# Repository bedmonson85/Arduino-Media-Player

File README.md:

Arduino-Media-Player
====================
This is currently a place to keep up with my eagle cad files for my project:
Atmega328p /w Arduino UNO bootloader based media player design. 
It is currently unfinished -- a work in progress.  After schematic and board are finished
I'll begin work on the code.

Released under the Creative Commons Attribution Share-Alike 4.0 License.
https:/creativecommons.org/licenses/by-sa/4.0/

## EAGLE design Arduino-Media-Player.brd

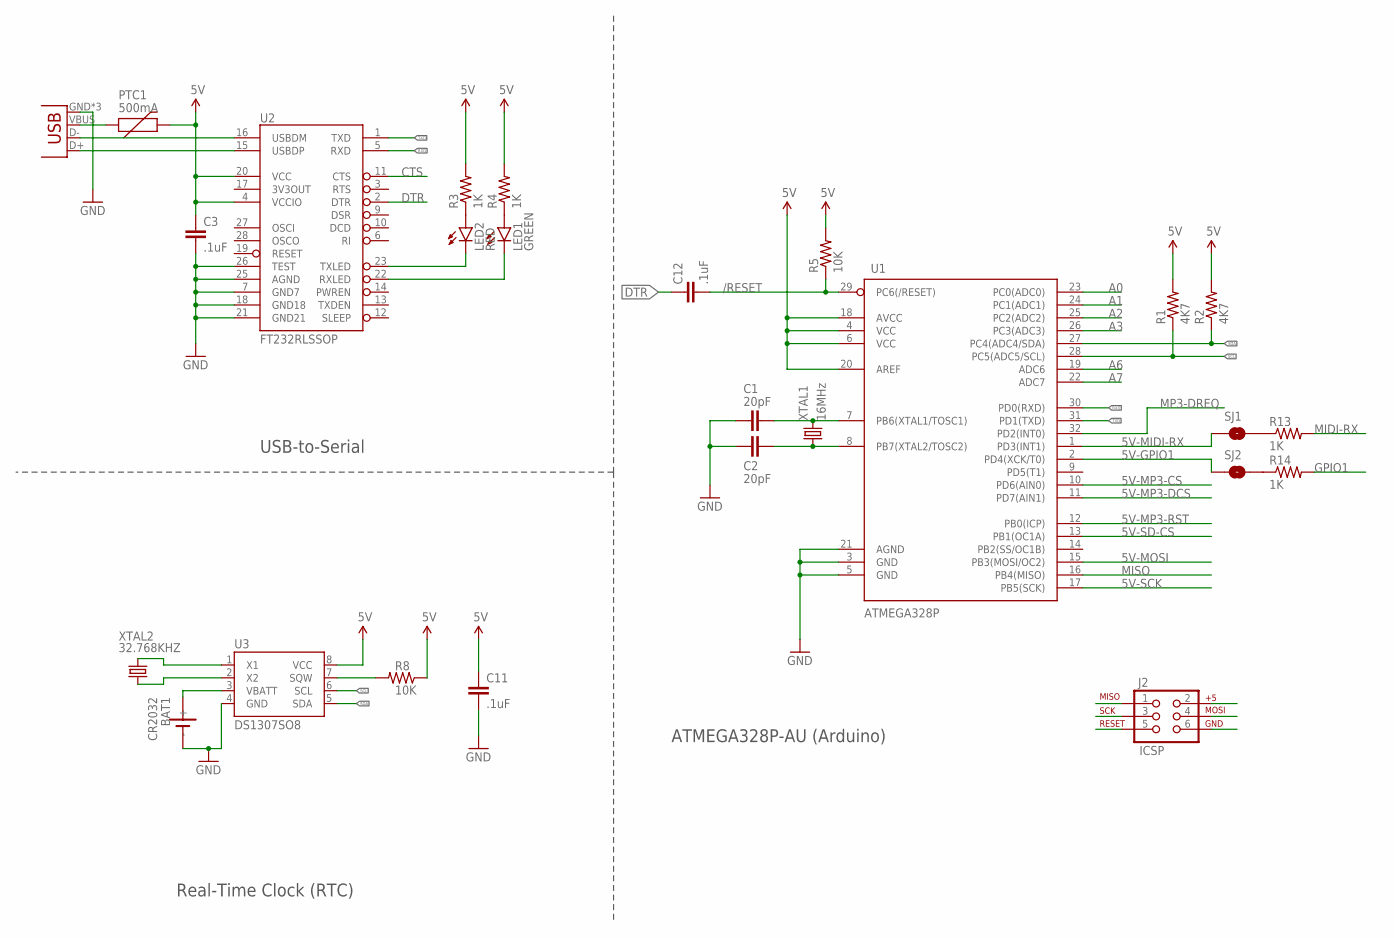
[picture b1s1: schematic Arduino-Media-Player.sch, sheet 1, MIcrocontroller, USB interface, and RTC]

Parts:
BAT1: CR2032; SN2032
C1, C2: 20pF; 1206
C3, C11, C12: .1uF; 0805
J2: ICSP; 2X3
LED1: GREEN; LED-0603
LED2: RED; LED-0603
PTC1: 500mA; 0805
R1, R2: 4K7; 0805
R3, R4, R13, R14: 1K; 0805
R5: 10K; 0805
R8: 10K; R0805W
SJ1, SJ2: JUMPER-PAD-2-NOROUND; PAD-JUMPER-2-NO_YES_SILK_ROUND
U1: ATMEGA328P; TQFP32-08
U2: FT232RLSSOP; SSOP28DB
U3: DS1307SO8; SO08
USB1: USB-MICROB
XTAL1: 16MHz; CRYSTAL-SMD-10.5X4.8-2PIN
XTAL2: 32.768KHZ; CRYSTAL-32KHZ-SMD

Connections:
5V: C3.1, C11.1, J2.2, PTC1.2, R1.2, R2.2, R3.2, R4.2, R5.2, R8.1, U1.4 (VCC), U1.6 (VCC), U1.18 (AVCC), U1.20 (AREF), U2.4 (VCCIO), U2.20 (VCC), U3.8 (VCC); also elsewhere on the board
5V-GPIO1: SJ2.1, U1.2 (PD4(XCK/T0))
5V-MIDI-RX: SJ1.1, U1.1 (PD3(INT1))
5V-MOSI: J2.4, U1.15 (PB3(MOSI/OC2)); also elsewhere on the board
5V-MP3-CS: U1.10 (PD6(AIN0)); also elsewhere on the board
5V-MP3-DCS: U1.11 (PD7(AIN1)); also elsewhere on the board
5V-MP3-RST: U1.12 (PB0(ICP)); also elsewhere on the board
5V-SCK: J2.3, U1.17 (PB5(SCK)); also elsewhere on the board
5V-SD-CS: U1.13 (PB1(OC1A)); also elsewhere on the board
/RESET: C12.2, J2.5, R5.1, U1.29 (PC6(/RESET))
A0: U1.23 (PC0(ADC0))
A1: U1.24 (PC1(ADC1))
A2: U1.25 (PC2(ADC2))
A3: U1.26 (PC3(ADC3))
A6: U1.19 (ADC6)
A7: U1.22 (ADC7)
CTS: U2.11 (CTS)
DS1307X1: U3.1 (X1), XTAL2.X2 (2)
DS1307X2: U3.2 (X2), XTAL2.X1 (1)
DTR: C12.1, U2.2 (DTR)
GND: BAT1.-, C1.1, C2.1, C3.2, C11.2, J2.6, U1.3 (GND), U1.5 (GND), U1.21 (AGND), U2.7 (GND7), U2.18 (GND18), U2.21 (GND21), U2.25 (AGND), U2.26 (TEST), U3.4 (GND), USB1.GND, USB1.MT1 (GND), USB1.MT2 (GND); also elsewhere on the board
GPIO1: R14.2; also elsewhere on the board
MIDI-RX: R13.2; also elsewhere on the board
MISO: J2.1, U1.16 (PB4(MISO)); also elsewhere on the board
MP3-DREQ: U1.32 (PD2(INT0)); also elsewhere on the board
unnamed: R13.1, SJ1.2
unnamed: R14.1, SJ2.2
unnamed: C1.2, U1.7 (PB6(XTAL1/TOSC1)), XTAL1.P$2 (2)
unnamed: C2.2, U1.8 (PB7(XTAL2/TOSC2)), XTAL1.P$1 (1)
unnamed: LED2.A, R3.1
unnamed: LED1.A, R4.1
unnamed: LED2.C, U2.23 (TXLED)
unnamed: LED1.C, U2.22 (RXLED)
unnamed: U2.16 (USBDM), USB1.D-
unnamed: U2.15 (USBDP), USB1.D+
RXD: U1.30 (PD0(RXD)), U2.5 (RXD)
SCL: R1.1, U1.28 (PC5(ADC5/SCL)), U3.6 (SCL)
SDA: R2.1, U1.27 (PC4(ADC4/SDA)), U3.5 (SDA)
SQW: R8.2, U3.7 (SQW)
TXD: U1.31 (PD1(TXD)), U2.1 (TXD)
VBATT: BAT1.+, U3.3 (VBATT)
VBUS: PTC1.1, USB1.VBUS

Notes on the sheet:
USB-to-Serial
Real-Time Clock (RTC)
ATMEGA328P-AU (Arduino)

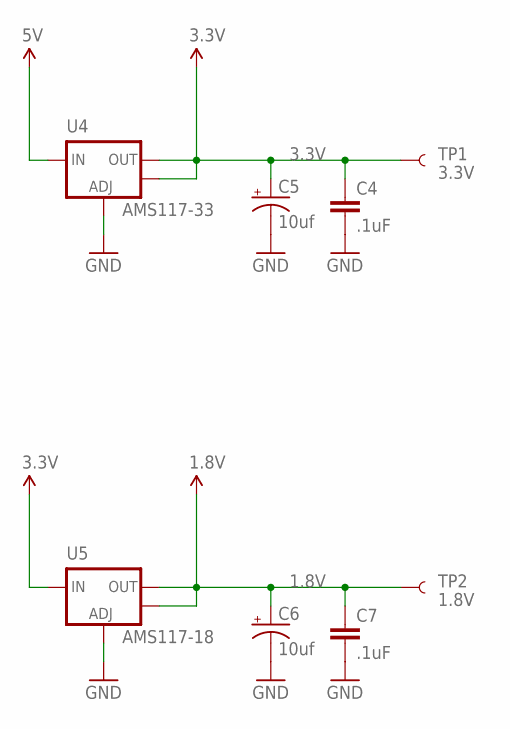
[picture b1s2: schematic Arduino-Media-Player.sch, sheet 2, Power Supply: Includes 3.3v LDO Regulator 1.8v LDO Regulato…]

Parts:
C4, C7: .1uF; 0805
C5, C6: 10uf; PANASONIC_C
TP1: 3.3V; PAD.03X.04
TP2: 1.8V; PAD.03X.04
U4: AMS117-33; SOT223
U5: AMS117-18; SOT223

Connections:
1.8V: C6.+, C7.1, TP2.P$1, U5.2 (OUT), U5.4 (OUT); also elsewhere on the board
3.3V: C4.1, C5.+, TP1.P$1, U4.2 (OUT), U4.4 (OUT), U5.3 (IN); also elsewhere on the board
5V: U4.3 (IN); also elsewhere on the board
GND: C4.2, C5.-, C6.-, C7.2, U4.1 (ADJ), U5.1 (ADJ); also elsewhere on the board

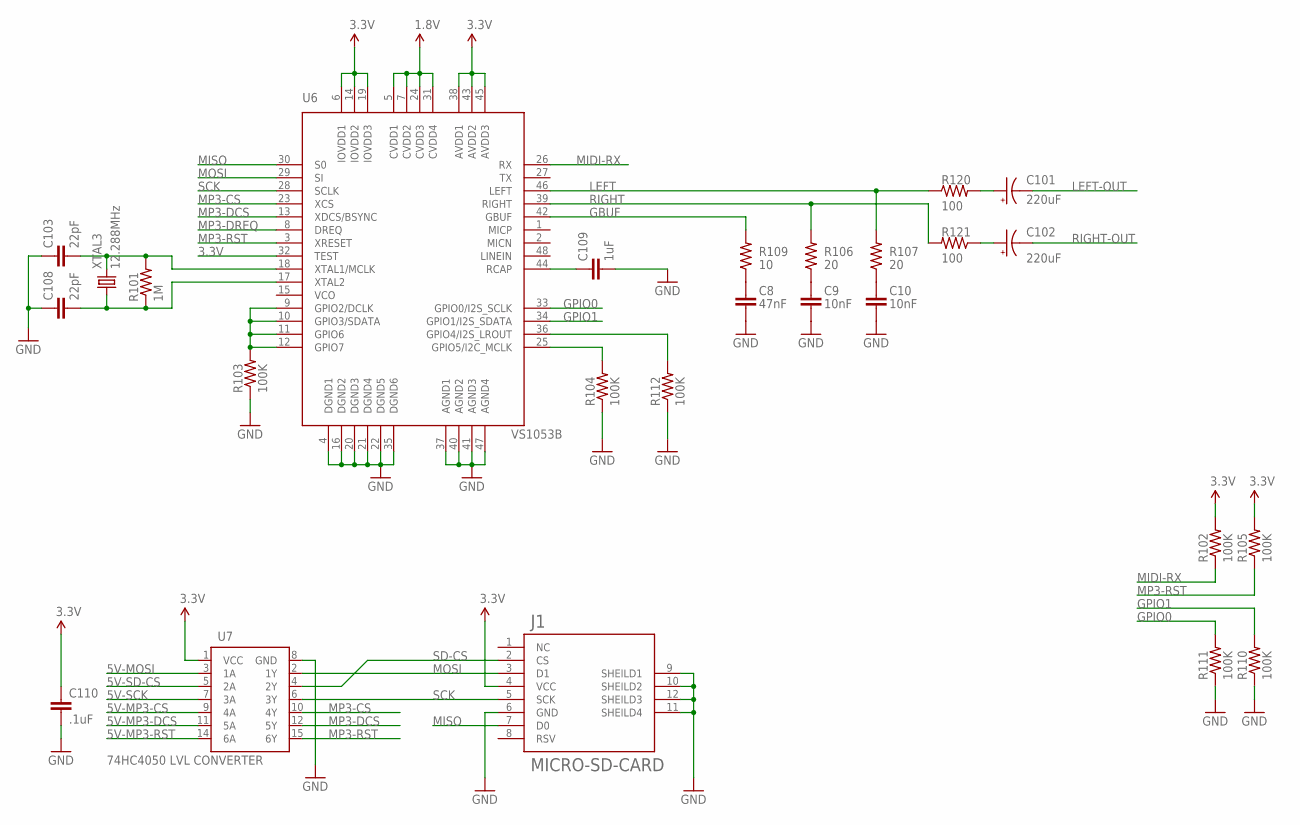
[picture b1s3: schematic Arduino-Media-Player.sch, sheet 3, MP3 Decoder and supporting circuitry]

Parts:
C8: 47nF; 0805
C9, C10: 10nF; 0805
C101, C102: 220uF; PANASONIC_G
C103, C108: 22pF; 0805
C109: 1uF; 0805
C110: .1uF; 0805
J1: MICRO-SD-CARD; MICRO-SD-EBAY
R101: 1M; 0805
R102, R103, R104, R105, R110, R111, R112: 100K; 0805
R106, R107: 20; 0805
R109: 10; 0805
R120, R121: 100; 0805
U6: VS1053B; LQFP-48
U7: 74HC4050 LVL CONVERTER; SO016
XTAL3: 12.288MHz; CRYSTAL-SMD-10.5X4.8-2PIN

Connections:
1.8V: U6.5 (CVDD1), U6.7 (CVDD2), U6.24 (CVDD3), U6.31 (CVDD4); also elsewhere on the board
3.3V: C110.1, J1.4 (VCC), R102.2, R105.2, U6.6 (IOVDD1), U6.14 (IOVDD2), U6.19 (IOVDD3), U6.32 (TEST), U6.38 (AVDD1), U6.43 (AVDD2), U6.45 (AVDD3), U7.1 (VCC); also elsewhere on the board
5V-MOSI: U7.3 (1A); also elsewhere on the board
5V-MP3-CS: U7.9 (4A); also elsewhere on the board
5V-MP3-DCS: U7.11 (5A); also elsewhere on the board
5V-MP3-RST: U7.14 (6A); also elsewhere on the board
5V-SCK: U7.7 (3A); also elsewhere on the board
5V-SD-CS: U7.5 (2A); also elsewhere on the board
GBUF: R109.2, U6.42 (GBUF)
GND: C8.1, C9.1, C10.1, C103.1, C108.1, C109.2, C110.2, J1.6 (GND), J1.9 (SHEILD1), J1.10 (SHEILD2), J1.11 (SHEILD4), J1.12 (SHEILD3), R103.1, R104.1, R110.1, R111.1, R112.1, U6.4 (DGND1), U6.16 (DGND2), U6.20 (DGND3), U6.21 (DGND4), U6.22 (DGND5), U6.35 (DGND6), U6.37 (AGND1), U6.40 (AGND2), U6.41 (AGND3), U6.47 (AGND4), U7.8 (GND); also elsewhere on the board
GPIO0: R111.2, U6.33 (GPIO0/I2S_SCLK)
GPIO1: R110.2, U6.34 (GPIO1/I2S_SDATA); also elsewhere on the board
LEFT: R107.2, R120.1, U6.46 (LEFT)
LEFT-OUT: C101.-
MIDI-RX: R102.1, U6.26 (RX); also elsewhere on the board
MISO: J1.7 (D0), U6.30 (S0); also elsewhere on the board
MOSI: J1.3 (D1), U6.29 (SI), U7.2 (1Y)
MP3-CS: U6.23 (XCS), U7.10 (4Y)
MP3-DCS: U6.13 (XDCS/BSYNC), U7.12 (5Y)
MP3-DREQ: U6.8 (DREQ); also elsewhere on the board
MP3-RST: R105.1, U6.3 (XRESET), U7.15 (6Y)
unnamed: C101.+, R120.2
unnamed: R104.2, U6.25 (GPIO5/I2C_MCLK)
unnamed: R112.2, U6.36 (GPIO4/I2S_LROUT)
unnamed: C102.+, R121.1
unnamed: C8.2, R109.1
unnamed: R103.2, U6.9 (GPIO2/DCLK), U6.10 (GPIO3/SDATA), U6.11 (GPIO6), U6.12 (GPIO7)
unnamed: C9.2, R106.1
unnamed: C10.2, R107.1
RCAP: C109.1, U6.44 (RCAP)
RIGHT: R106.2, R121.2, U6.39 (RIGHT)
RIGHT-OUT: C102.-
SCK: J1.5 (SCK), U6.28 (SCLK), U7.6 (3Y)
SD-CS: J1.2 (CS), U7.4 (2Y)
VS1053XTAL1: C103.2, R101.2, U6.18 (XTAL1/MCLK), XTAL3.P$2 (2)
VS1053XTAL2: C108.2, R101.1, U6.17 (XTAL2), XTAL3.P$1 (1)

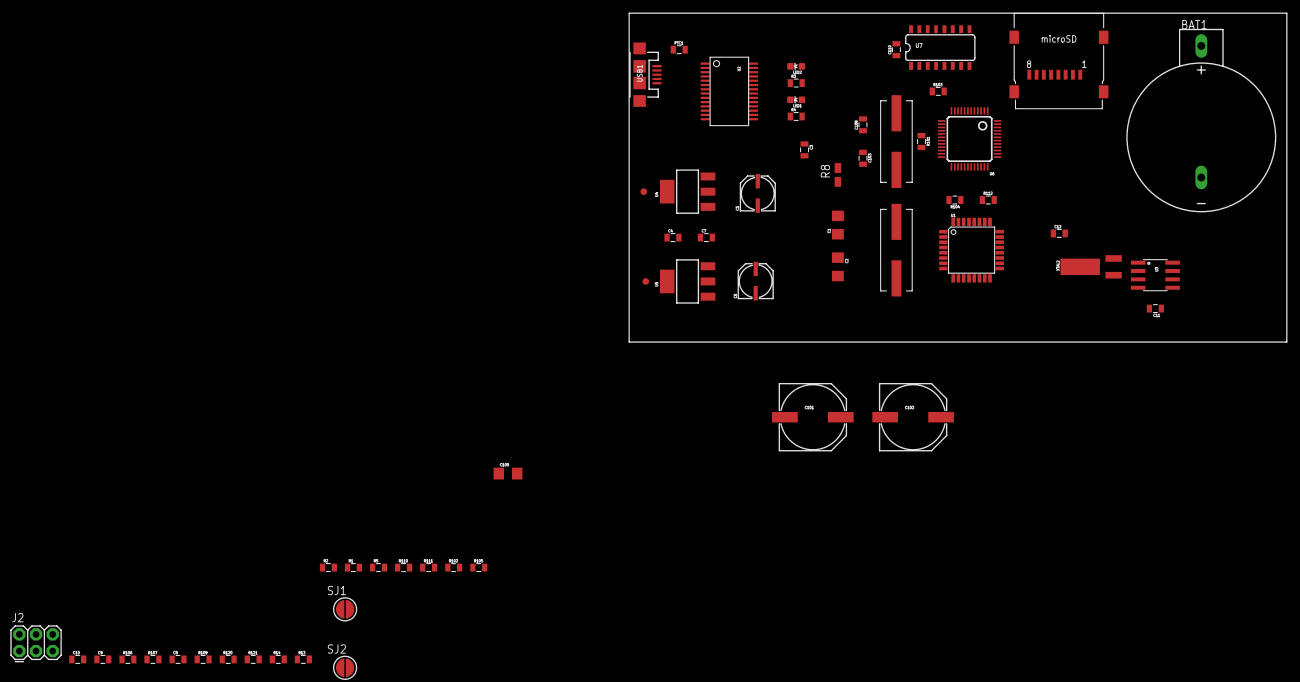
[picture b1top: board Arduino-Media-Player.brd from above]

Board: 2 copper layers, 100.0 x 50.0 mm, 60 parts (0 on the bottom side), 58 nets.

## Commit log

2014-09-03 README update
2014-09-03 Added eagle cad schematic and board files
2014-09-21 Few minor changes
2014-09-21 Moved different sections to separate sheets.
2014-09-21 More minor changes
2014-09-27 Added audio output circuitry for mp3 decoder
2014-09-27 Added ICSP header for ATMEGA328p

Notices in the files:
parts and their libraries:
SparkFun-DigitalIC: Licensing: Creative Commons ShareAlike 4.0 International - https://creativecommons.org/licenses/by-sa/4.0
